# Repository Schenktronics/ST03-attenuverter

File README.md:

<picture>
  <source media="(prefers-color-scheme: dark)" srcset="docs/images/logo-light.png">
  
</picture>

# ST-03 Attenuverter

A 6HP Eurorack quad attenuverter from **Schenktronics**. Each of its four channels scales a signal anywhere from x1, through zero, to x-1 (inverted). Every input is normalled to +5 V, so with nothing plugged in, each channel is a manual offset from -5 V to +5 V.

## Features

- 6HP, 20 mm deep. 16 mA on +12 V and 9 mA on -12 V.
- Four channels, each turning a signal down, off, or inverting it
- Knobs with a printed zero mark at the top of their travel
- Inputs normalled to +5 V: four manual offset voltages when nothing's plugged in
- Reverse-power protection on both rails
- Kits come with the surface-mount parts already soldered and tested: 54 through-hole joints to build

## Documentation

| Document | For | PDF |
|----------|-----|-----|
| [User Manual](docs/manual.md) | Using the module | [PDF](docs/pdf/ST-03_Attenuverter_User_Manual.pdf) |
| [Assembly Guide](docs/assembly-guide.md) | Building the kit | [PDF](docs/pdf/ST-03_Attenuverter_Assembly_Guide.pdf) |
| [Bill of Materials](docs/BOM.md) ([CSV](docs/BOM.csv)) | Parts and sourcing | |

## Repository layout

```
hardware/
  ST-03_Attenuverter.step          3D model of the assembled module
  attenuverter/                    Main PCB (KiCad 10)
    Attenuverter.kicad_sch           Schematic
    Attenuverter.kicad_pcb           PCB layout
    Attenuverter.step                3D model
    attenuverter BOM.xlsx            Original BOM spreadsheet
  panel/                           Faceplate (KiCad 10, made as an aluminum PCB)
    AttenuverterFaceplate.kicad_pcb  Faceplate layout
    AttenuverterFaceplate.step       3D model
docs/                              Manual, assembly guide, BOM, images
  pdf/                               PDF versions of the manual and assembly guide
```

The `.github/` folder holds the automation that builds the PDFs. You can ignore it.

## Fabrication

| Board | Size | Layers | Thickness | Notes |
|-------|------|--------|-----------|-------|
| Main PCB | 30 x 100 mm | 2 | 1.6 mm | Standard green is fine. Surface-mount parts on the back. |
| Faceplate | 30 x 128.5 mm | 1 | 1.6 mm | Aluminum PCB, white solder mask, black silkscreen. Only the front copper layer is used, so FR4 works too. |

## Sourcing your own parts

The [BOM](docs/BOM.md) lists every part, including the surface-mount ones the kits ship with already soldered. The jack pads are oval so the board can also take panel-mount style jacks, which may be easier to source. The CUI MJ-3507 is one example: its sleeve is a solder lug rather than a pin, so each one needs a short wire from that lug to the jack's square pad.

## License

This hardware design and its documentation are licensed under [CC BY-NC-SA 4.0](https://creativecommons.org/licenses/by-nc-sa/4.0/). See [LICENSE](LICENSE).

The Schenktronics name and logo are trademarks of Schenktronics LLC and are not covered by the CC BY-NC-SA 4.0 license.

## Links

- Shop: <https://schenktronics.com/product/st-03/>
- Docs page: <https://schenktronics.com/docs/st-03/>
- Website: <https://schenktronics.com>

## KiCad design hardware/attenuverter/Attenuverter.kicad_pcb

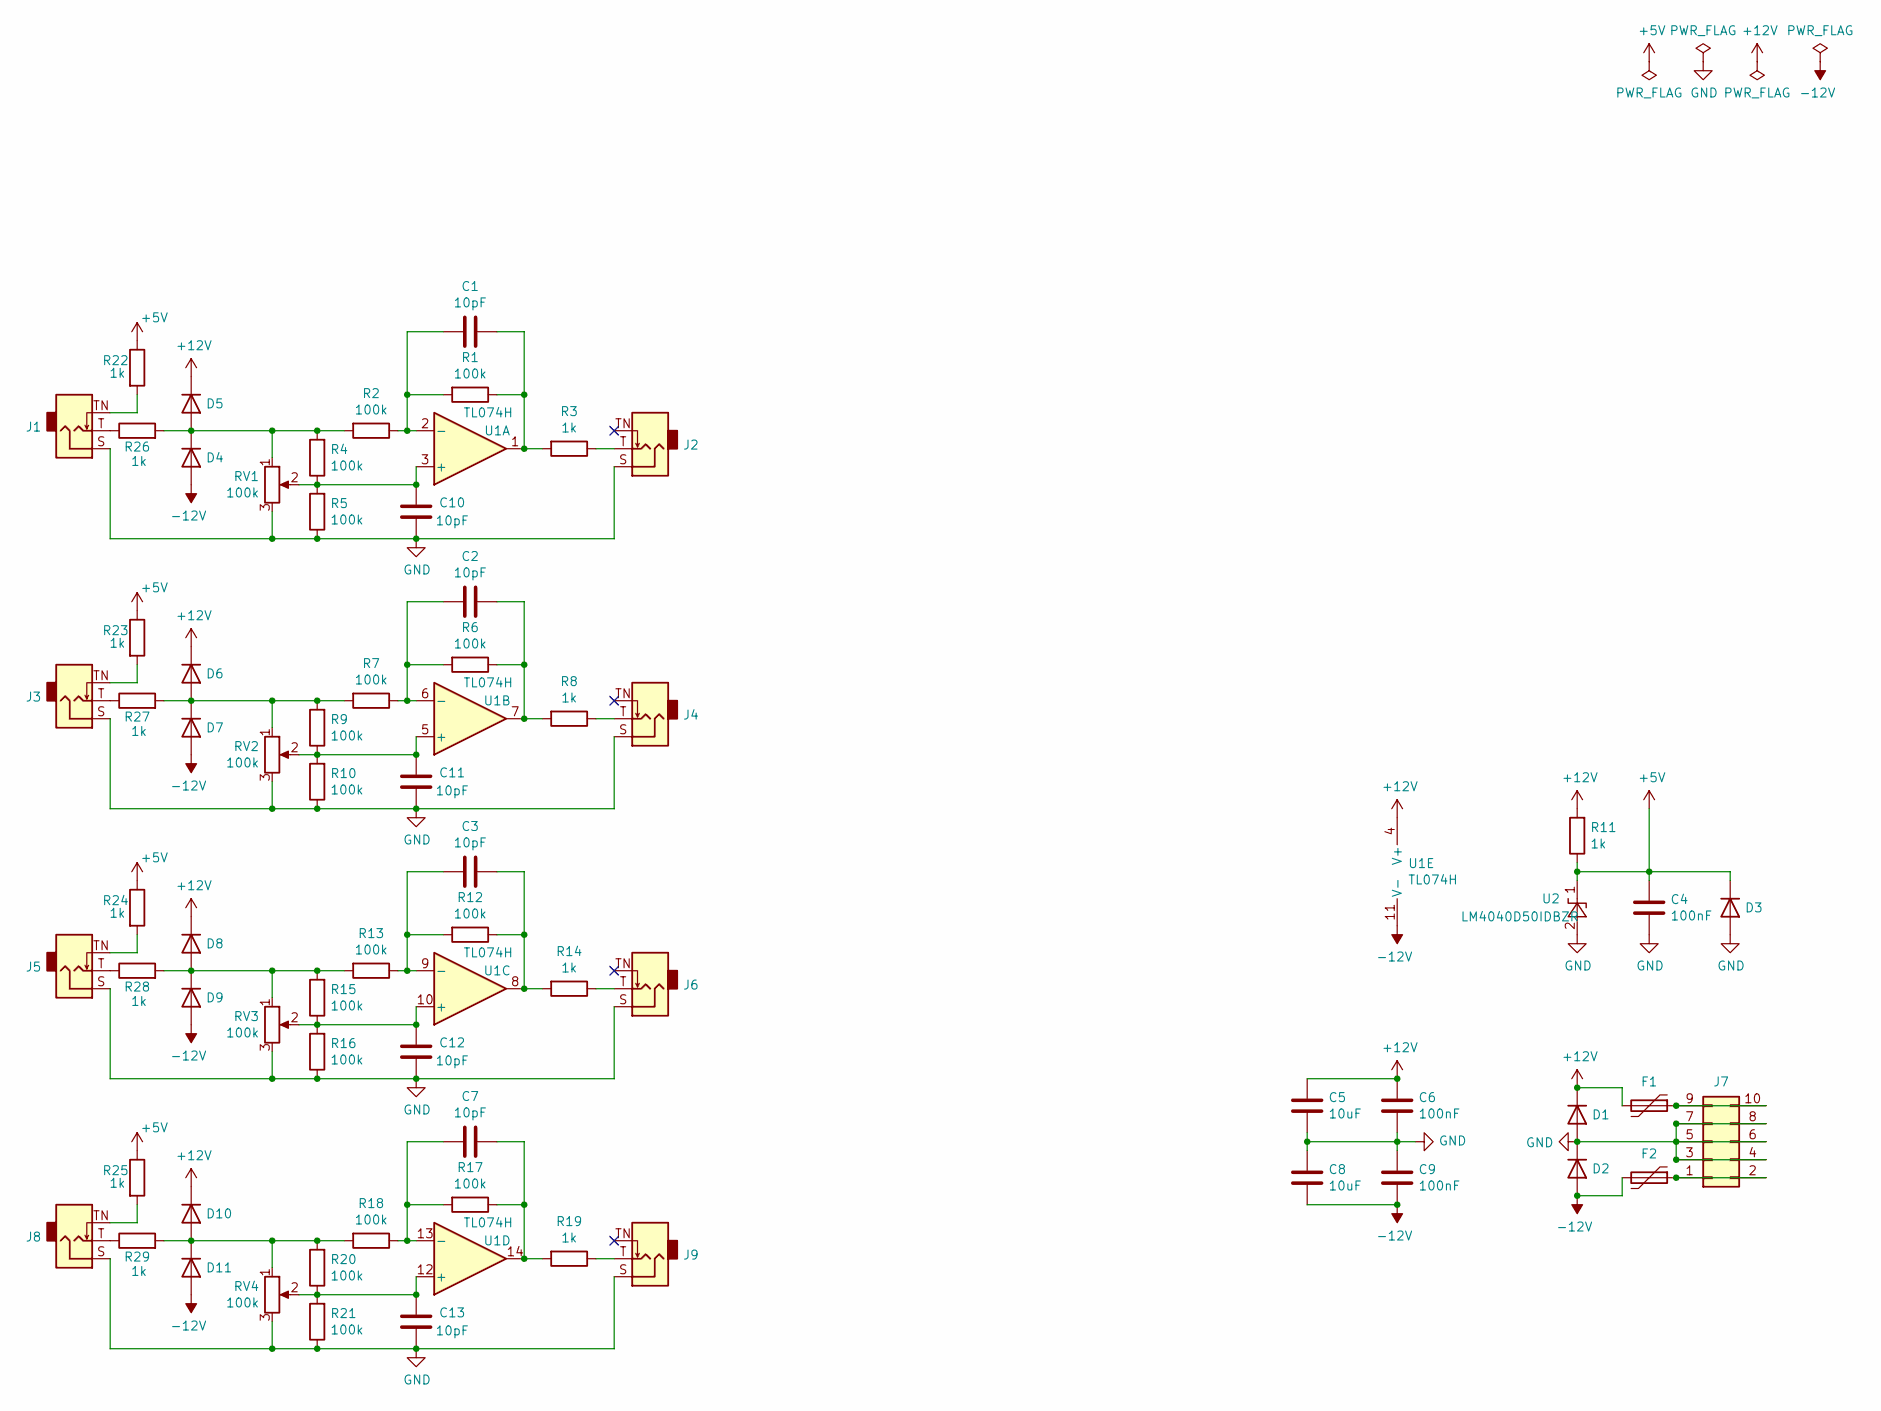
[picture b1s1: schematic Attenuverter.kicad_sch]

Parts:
C1, C2, C3, C7, C10, C11, C12, C13: 10pF; C_0805_2012Metric
C4, C6, C9: 100nF; C_0805_2012Metric
C5, C8: 10uF; C_0805_2012Metric
D1, D2: D; D_SMA
D3, D4, D5, D6, D7, D8, D9, D10, D11: 1N4148WS-7-F; D_SOD-323
F1, F2: Polyfuse; Fuse_1206_3216Metric
J1, J2, J3, J4, J5, J6, J8, J9: AudioJack2_SwitchT; Jack_3.5mm_QingPu_WQP-PJ398SM_Vertical_CenterHole_OvalPads
J7: Conn_02x05_Odd_Even; PinHeader_2x05_P2.54mm_Vertical_Shrouded
R1, R2, R4, R5, R6, R7, R9, R10, R12, R13, R15, R16, R17, R18, R20, R21: 100k; R_0805_2012Metric
R3, R8, R11, R14, R19, R22, R23, R24, R25, R26, R27, R28, R29: 1k; R_0805_2012Metric
RV1, RV2, RV3, RV4: 100k; Potentiometer_Alps_RK09L_Plated_Mount_Holes
U1: TL074H; SOIC-14_3.9x8.7mm_P1.27mm
U2: LM4040D50IDBZR; SOT-23

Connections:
+5V: C4.1, D3.1 (K), R11.1, R22.1, R23.1, R24.1, R25.1, U2.1 (K)
+12V: C5.1, C6.1, D1.1 (K), D5.1 (K), D6.1 (K), D8.1 (K), D10.1 (K), F1.2, R11.2, U1.4 (V+)
-12V: C8.2, C9.2, D2.2 (A), D4.2 (A), D7.2 (A), D9.2 (A), D11.2 (A), F2.2, U1.11 (V-)
GND: C4.2, C5.2, C6.2, C8.1, C9.1, C10.2, C11.2, C12.2, C13.2, D1.2 (A), D2.1 (K), D3.2 (A), J1.S, J2.S, J3.S, J4.S, J5.S, J6.S, J7.3, J7.4, J7.5, J7.6, J7.7, J7.8, J8.S, J9.S, R5.1, R10.1, R16.1, R21.1, RV1.3, RV2.3, RV3.3, RV4.3, U2.2 (A)
unnamed: C1.1, R1.1, R3.2, U1.1
unnamed: C2.1, R6.1, R8.2, U1.7
unnamed: C3.1, R12.1, R14.2, U1.8
unnamed: C7.1, R17.1, R19.2, U1.14
unnamed: D4.1 (K), D5.2 (A), R2.2, R4.2, R26.2, RV1.1
unnamed: D6.2 (A), D7.1 (K), R7.2, R9.2, R27.2, RV2.1
unnamed: D8.2 (A), D9.1 (K), R13.2, R15.2, R28.2, RV3.1
unnamed: D10.2 (A), D11.1 (K), R18.2, R20.2, R29.2, RV4.1
unnamed: J1.T, R26.1
unnamed: J1.TN, R22.2
unnamed: J2.T, R3.1
unnamed: J3.T, R27.1
unnamed: J3.TN, R23.2
unnamed: J4.T, R8.1
unnamed: J5.T, R28.1
unnamed: J5.TN, R24.2
unnamed: J6.T, R14.1
unnamed: F2.1, J7.1, J7.2
unnamed: F1.1, J7.9, J7.10
unnamed: J8.T, R29.1
unnamed: J8.TN, R25.2
unnamed: J9.T, R19.1
unnamed: C10.1, R4.1, R5.2, RV1.2, U1.3 (+)
unnamed: C1.2, R1.2, R2.1, U1.2 (-)
unnamed: C11.1, R9.1, R10.2, RV2.2, U1.5 (+)
unnamed: C2.2, R6.2, R7.1, U1.6 (-)
unnamed: C12.1, R15.1, R16.2, RV3.2, U1.10 (+)
unnamed: C3.2, R12.2, R13.1, U1.9 (-)
unnamed: C13.1, R20.1, R21.2, RV4.2, U1.12 (+)
unnamed: C7.2, R17.2, R18.1, U1.13 (-)

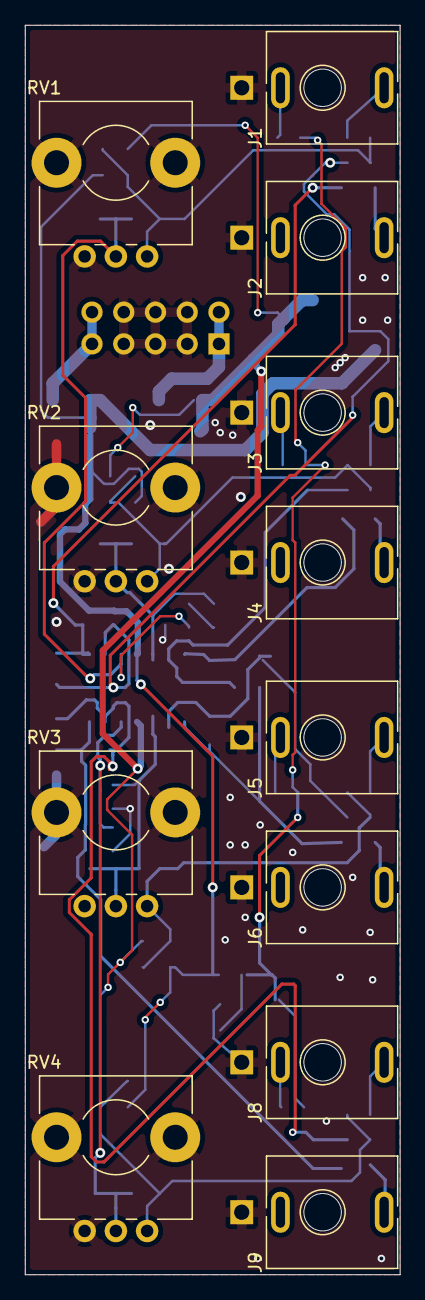
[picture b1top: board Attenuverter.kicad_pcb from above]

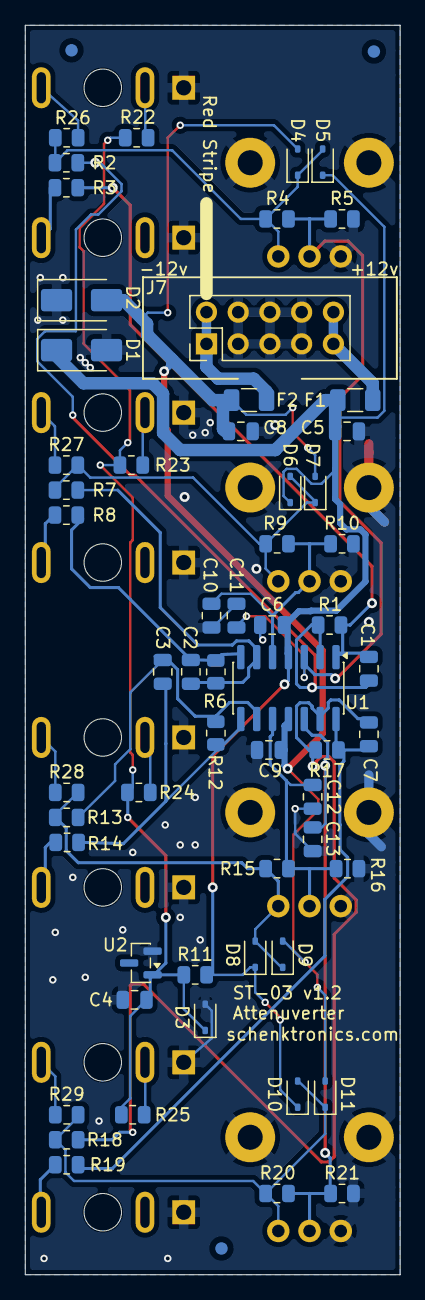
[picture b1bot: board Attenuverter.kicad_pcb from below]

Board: 2 copper layers, 30.0 x 100.0 mm, 73 parts (61 on the bottom side), 34 nets.

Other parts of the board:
FID1, FID2, FID3: Fiducial_1mm_Mask2mm

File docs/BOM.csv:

Qty,Reference,Description,Manufacturer,Part Number,Link
1,U1,"Quad JFET op-amp, SOIC-14. Use TI, Microchip or Analog Devices only",Texas Instruments,TL074CDR,https://www.ti.com/lit/ds/symlink/tl074.pdf
1,U2,"5.0V shunt voltage reference, SOT-23-3, cathode pin 1, anode pin 2. Use TI, Microchip or Analog Devices only",Texas Instruments,LM4040DIM3X-5.0/NOPB,https://www.ti.com/lit/ds/symlink/lm4040.pdf
16,"R1, R2, R4, R5, R6, R7, R9, R10, R12, R13, R15, R16, R17, R18, R20, R21","Resistor, 100k, 1%, 0805",Yageo,RC0805FR-07100KL,
13,"R3, R8, R11, R14, R19, R22, R23, R24, R25, R26, R27, R28, R29","Resistor, 1k, 1%, 0805",Yageo,RC0805FR-071KL,
4,"C1, C2, C3, C7","Capacitor, 10pF, 50V, C0G/NP0, 0805",Yageo,CC0805JRNPO9BN100,
3,"C4, C6, C9","Capacitor, 100nF, 25V, X7R, 0805",AVX,08053C104KAT2A,
2,"C5, C8","Capacitor, 10uF, 25V, X5R, 0805",Taiyo Yuden,TMK212BBJ106KG-T,
2,"D1, D2","Diode, 1A, 300V, SMA",ON Semiconductor,MRA4003T3G,
9,"D3, D4, D5, D6, D7, D8, D9, D10, D11","Diode, 1N4148, SOD-323, 75 V, 150 mA","Diodes Incorporated, or equivalent",1N4148WS-7-F,https://datasheet.octopart.com/1N4148WS-7-F-Diodes-Inc.-data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
2,"F1, F2","Resettable fuse (PTC), 200mA hold, 30V, 1206",Bel Fuse,0ZCJ0020FF2E,
1,J7,"Shrouded pin header, 2x5, 2.54mm, vertical",On Shore Technology,302-S101,
8,"J1-J6, J8, J9","3.5mm mono switched jack, vertical, with nut (CUI MJ-3507 also works, with a ground wire from its sleeve lug to the square pad)",QingPu,WQP-PJ398SM or WQP518MA,http://www.qingpu-electronics.com/en/products/WQP-PJ398SM-362.html
4,RV1-RV4,"Potentiometer, 100k linear, 9mm, center detent, bushingless, 25mm D shaft (or equivalent)",Bourns,PTV09A-4225F-B104,https://www.bourns.com/docs/Product-Datasheets/PTV09.pdf
4,,"Knob, fits 6mm D shaft (or equivalent)",Davies Molding,1221-J,
1,,"Main PCB, 30x100mm, 2-layer, 1.6mm",Schenktronics,Attenuverter v1.0,
1,,"Faceplate, 6HP, 1.6mm aluminium PCB",Schenktronics,Attenuverter Faceplate,
1,,"Eurorack power cable, 10-pin to 16-pin",,,
